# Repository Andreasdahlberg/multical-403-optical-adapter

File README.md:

# Optical Adapter for Multical 403

## Table of Contents
1. [Introduction](#introduction)
2. [Features](#features)
3. [Assembly Instructions](#assembly-instructions)
4. [Software](#software)
5. [Usage](#usage)
6. [Troubleshooting](#troubleshooting)

## Introduction

This project provides an optical adapter designed for the Kamstrup Multical 403 heat meter, allowing you to interface with it via serial communication.

**⚠️ WARNING: This project is work in progress and currently untested. Use at your own risk.**

## Features
* On demand activation of the Multical optical interface to reduce power consumption.
* Powered with 5V DC via USB or external power supply.
* Compatible with 3.3V FTDI USB cable.

## Assembly Instructions

### PCB Verification

Before soldering the components, it is recommended to perform the following checks on the PCB to
ensure there are no manufacturing defects:

1. Verify the coil resistance, this can be done by measuring the resistance between the pads
    connected to the coil on the two coil resistors (R10 and R11). The expected resistance should
    be around 18Ω(assuming OSHPark standard 4-layer stackup).

1. Check for short circuits between the 5V, 3V3 and GND pads. 5V and GND is available on the pin
    header while 3V3 is available on the voltage regulator output. There should be no continuity
    between these pads.

### Assembly

1. Solder the components onto the PCB according to the provided BOM and PCB layout. Note that the pin
    header should be soldered on the bottom side of the PCB, while all other components should be
    soldered on the top side. Check out the interactive BOM for component placement and reference
    designators.

    > Tip: Start with the power supply components (voltage regulator, capacitors, and resistors) to
    > ensure the board is powered correctly before soldering the remaining components.

1. Close the J1 solder bridge, it should only be open for testing purposes.

### Mounting

1. Connect a 3.3V FTDI USB cable to the pin header, ensuring the correct orientation. The board is
    designed to be powered by the 5V from the FTDI cable.

1. Mount the optical adapter onto the Multical 403 heat meter's optical interface, the guide holes
    on the PCB should align with the pins on the heat meter. Use double-sided tape on the back of
    the PCB to secure it in place if necessary.

### Bill of Materials

[BOM](https://andreasdahlberg.github.io/multical-403-optical-adapter/bom/optical_adapter-bom.html)

[Interactive BOM](https://andreasdahlberg.github.io/multical-403-optical-adapter/bom/optical_adapter-ibom.html)

## Software

🚧 Work in progress

There is currently no specific software available for interfacing with the optical adapter but
existing tools, such as [PyKMP](https://github.com/gertvdijk/PyKMP) should work. One exception is
the activation of the optical interface, which will require custom code to toggle the activation
pin on the adapter.

## Usage

🚧 Work in progress

## Troubleshooting

🚧 Work in progress

## License

This project is released as **Open Source Hardware** under the [CERN Open Hardware License v2](LICENSE). You are free to use, modify, manufacture, and distribute this hardware, provided you comply with the terms of the license.

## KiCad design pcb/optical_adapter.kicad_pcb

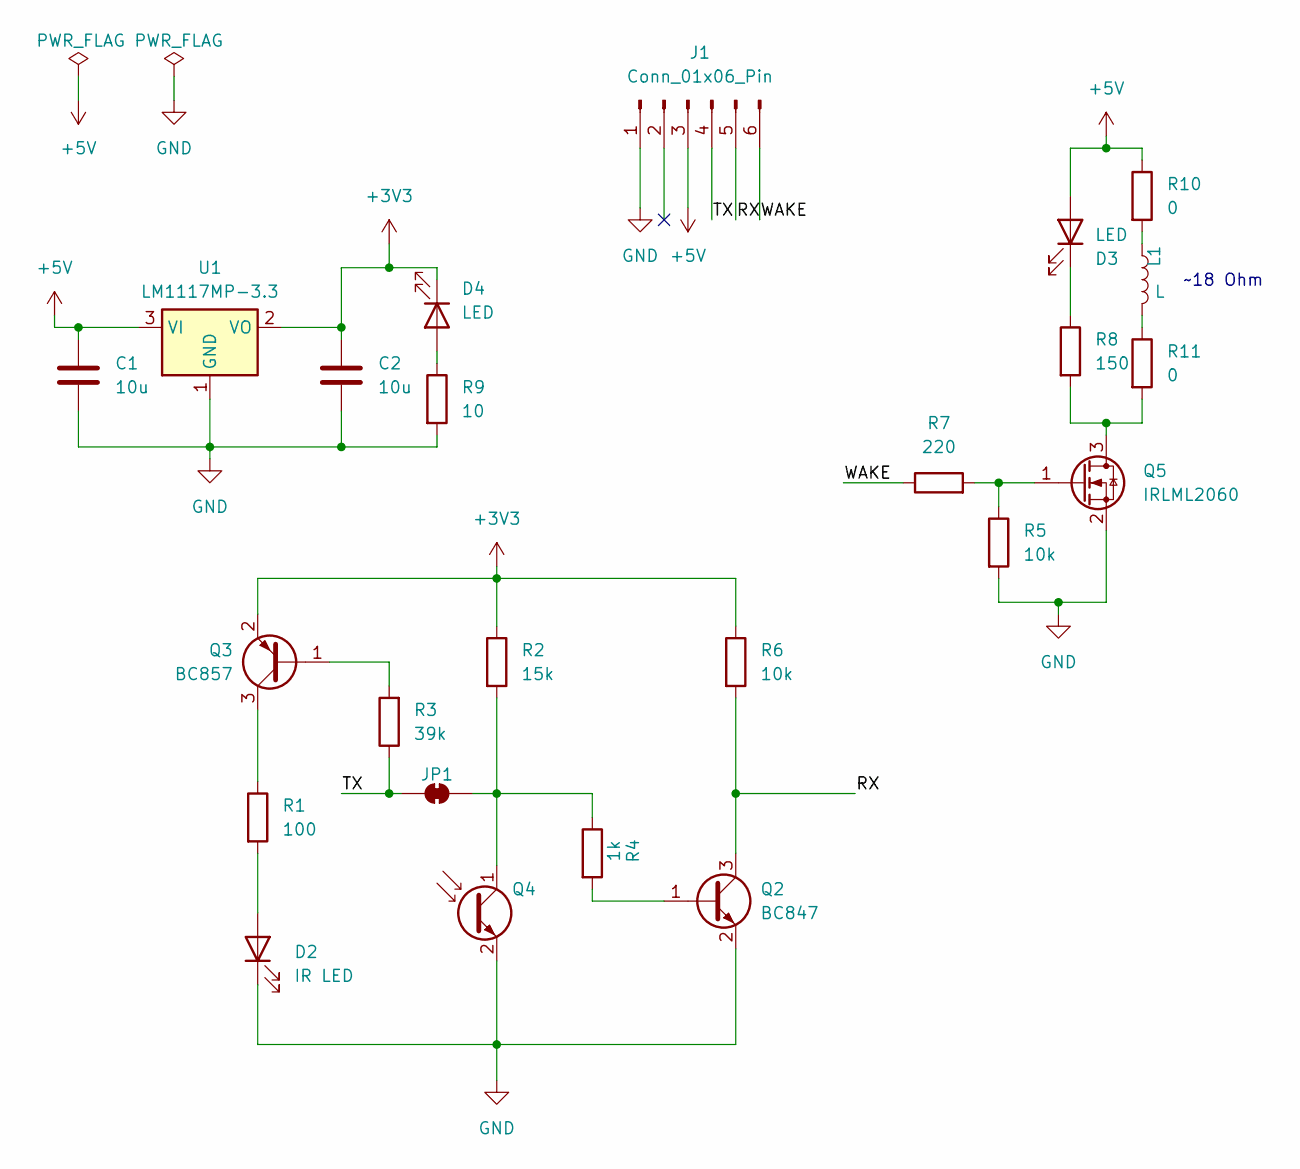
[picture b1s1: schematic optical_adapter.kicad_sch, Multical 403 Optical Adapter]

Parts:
C1, C2: 10u; C_1206_3216Metric_Pad1.33x1.80mm_HandSolder; MOUSERNO 74-TR3A106K010C1000
D2: IR LED; kingbright_heli_r; MOUSERNO 604-APTR3216F3C
D3: LED; LED_1206_3216Metric_Pad1.42x1.75mm_HandSolder; MOUSERNO 710-150120AS75000
D4: LED; LED_1206_3216Metric_Pad1.42x1.75mm_HandSolder; MOUSERNO 710-150120GS75000
J1: Conn_01x06_Pin; PinHeader_1x06_P2.54mm_Vertical; MOUSERNO 649-68001-406HLF
JP1: SolderJumper_2_Bridged; SolderJumper-2_P1.3mm_Open_TrianglePad1.0x1.5mm
L1: L; 4l_26_turn_16_dia_5_mil
Q2: BC847; SOT-23; MOUSERNO 863-BC847CLT1G
Q3: BC857; SOT-23; MOUSERNO 863-BC857CLT1G
Q4: Q_Photo_NPN; kingbright_heli_r; MOUSERNO 604-APTR3216P3BT
Q5: IRLML2060; SOT-23; MOUSERNO 942-IRLML2060TRPBF
R1: 100; R_1206_3216Metric_Pad1.30x1.75mm_HandSolder; MOUSERNO 71-CRCW1206J-100-E3
R2: 15k; R_1206_3216Metric_Pad1.30x1.75mm_HandSolder; MOUSERNO 71-CRCW1206J-15K-E3
R3: 39k; R_1206_3216Metric_Pad1.30x1.75mm_HandSolder; MOUSERNO 71-CRCW1206J-39K-E3
R4: 1k; R_1206_3216Metric_Pad1.30x1.75mm_HandSolder; MOUSERNO 71-CRCW1206J-15K-E3
R5, R6: 10k; R_1206_3216Metric_Pad1.30x1.75mm_HandSolder; MOUSERNO 71-CRCW1206J-10K-E3
R7: 220; R_1206_3216Metric_Pad1.30x1.75mm_HandSolder; MOUSERNO 71-CRCW1206J-220-E3
R8: 150; R_1206_3216Metric_Pad1.30x1.75mm_HandSolder; MOUSERNO 71-CRCW1206J-150-E3
R9: 10; R_1206_3216Metric_Pad1.30x1.75mm_HandSolder; MOUSERNO 71-CRCW1206J-10-E3
R10, R11: 0; R_1206_3216Metric_Pad1.30x1.75mm_HandSolder; MOUSERNO 71-CRCW12060000ZSTC
U1: LM1117MP-3.3; SOT-223-3_TabPin2; MOUSERNO 926-LM1117MP-3.3NOPB

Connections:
+3V3: C2.1, D4.1 (K), Q3.2 (E), R2.1, R6.1, U1.2 (VO)
+5V: C1.1, D3.2 (A), J1.3, R10.1, U1.3 (VI)
/RX: J1.5, Q2.3 (C), R6.2
/TX: J1.4, JP1.1 (A), R3.1
/WAKE: J1.6, R7.1
GND: C1.2, C2.2, D2.1 (K), J1.1, Q2.2 (E), Q4.2 (E), Q5.2 (S), R5.2, R9.2, U1.1 (GND)
unnamed: D2.2 (A), R1.2
unnamed: D3.1 (K), R8.1
unnamed: D4.2 (A), R9.1
unnamed: JP1.2 (B), Q4.1 (C), R2.2, R4.1
unnamed: L1.1, R10.2
unnamed: L1.2, R11.1
unnamed: Q2.1 (B), R4.2
unnamed: Q3.1 (B), R3.2
unnamed: Q3.3 (C), R1.1
unnamed: Q5.3 (D), R8.2, R11.2
unnamed: Q5.1 (G), R5.1, R7.2

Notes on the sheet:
~18 Ohm

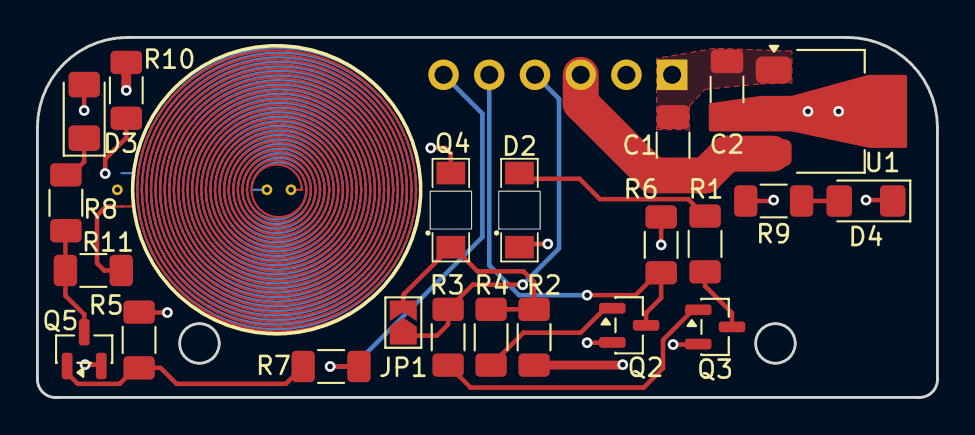
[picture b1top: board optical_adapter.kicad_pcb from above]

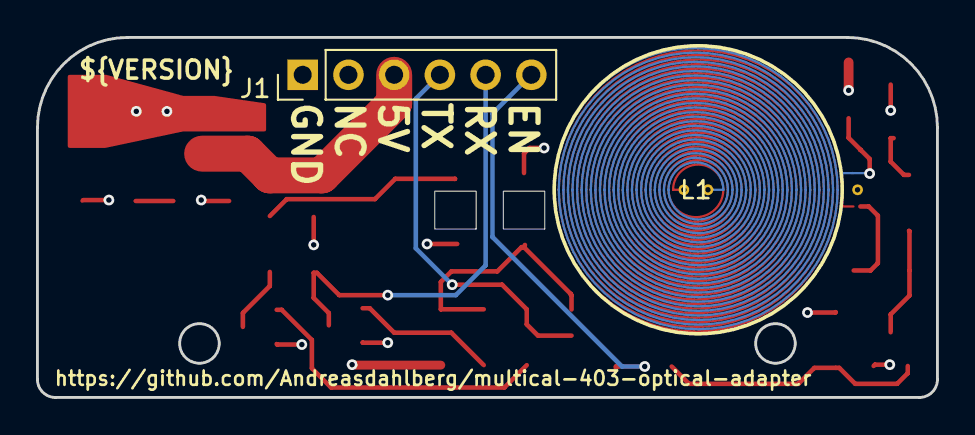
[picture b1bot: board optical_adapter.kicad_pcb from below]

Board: 4 copper layers, 50.0 x 20.0 mm, 24 parts (2 on the bottom side), 17 nets.

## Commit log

2025-01-08 Add license and readme
2025-01-08 Add gitignore
2025-01-10 Add PCB shape design file
2025-01-10 Add Kicad project
2025-01-10 Rename PCB outline file
2025-01-10 Restructure pcb directory
2025-01-10 Implement Kibot CI workflow
2025-01-10 Add CI status badge to README
2025-01-10 Use kicad 8 image for Kibot CI workflows
2025-01-13 Add PCB coil footprint
2025-01-13 Add power supply circuit
2025-01-13 Add IR RX/TX circuit
2025-01-13 Rough PCB component layout
2025-01-13 Remove empty remap option from kibot draw config
2025-01-14 Add coil driver circuit
2025-01-14 Add power LED to 3V3 rail
2025-01-14 Update layout with coil driver components
2025-01-18 Add 0 Ohms resistors to the coil
    They make it possible to limit the current if needed and make
    it easier to patch, e.g. change direction.
2025-01-18 Remove solder bridge between VBUS and +5V
2025-01-18 Route power supply
2025-01-21 Update PCB layout
    All traces are routed.
2025-08-24 Update KiCad files to version 9
2025-08-24 Use KiCad 9 container for KiBot workflow
2025-08-24 Update to actions/checkout@v4 in workflows
2025-08-24 Update mismatched footprints
2025-12-25 Update project settings
2025-12-27 Add part numbers to BOM
2025-12-27 Add solder bridge between TX and RX circuit
2025-12-29 Fix the coil active LED
    Changed to 150 Ohm to better suite the amber LED and fix incorrect
    rotation.
2025-12-29 Update symbols
2025-12-29 Add new PCB coil footprint
2025-12-29 Move the coil wake up signal to RTS
2025-12-29 Update kingbright LED footprint
    Adjusted the silkscreen so that it does not overlap with the pads.
2025-12-29 Add missing datasheet link for the IR-LED
2026-01-07 Update README
    Added a WIP warning and an image of the PCB.
2026-01-07 Add doc deployment to Github pages
2026-01-27 Fix DRC warnings
2026-01-27 Update footprints
2026-01-27 Update kibot config
2026-01-27 Add BOM links to README
2026-03-06 Fix incorrect datasheet URL
2026-03-06 Add ignore rule for hole clearance
    The coil generator plugin created the holes that triggered the warnings,
    but it should be ok to manufacture.
2026-03-06 Increase radius of guide holes
    This required the coil to be moved upwards to make place for the
    bigger holes.
2026-03-06 Add OSHW logo to the PCB
2026-03-06 Update DRC exclusions
2026-03-06 Update README
    Added license information in the README.
2026-03-07 Use variable for board version
2026-03-07 Add release workflow
    This workflow will package a release on tags with the Kicad files.
2026-03-07 Update version in PCB file on release
2026-03-07 Fix failing deployments on tags
2026-03-07 Update README
    Added assembly instructions and software info.
2026-04-07 Fix #4
    Swap silkscreen designator for R1 and R6
2026-04-07 Add datasheet for power LED
2026-04-07 Fix #1
    Increase the value of the power LED resistor since the LED was to
    bright.
2026-04-07 Fix #5
    Change D1 to Q4(phototransistor)
2026-04-07 Redesign RX circuit
